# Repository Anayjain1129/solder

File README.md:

# Simple PCB that glows up
Submission for Solder YSWS

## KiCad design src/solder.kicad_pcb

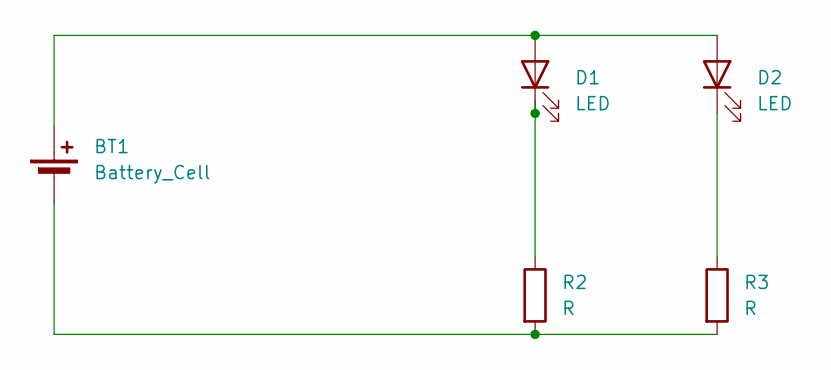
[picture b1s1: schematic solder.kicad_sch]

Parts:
BT1: Battery_Cell; BatteryHolder_Keystone_3034_1x20mm
D1, D2: LED; LED_D5.0mm
R2, R3: R; R_Axial_DIN0207_L6.3mm_D2.5mm_P7.62mm_Horizontal

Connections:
unnamed: BT1.1 (+), D1.2 (A), D2.2 (A)
unnamed: BT1.2 (-), R2.2, R3.2
unnamed: D1.1 (K), R2.1
unnamed: D2.1 (K), R3.1

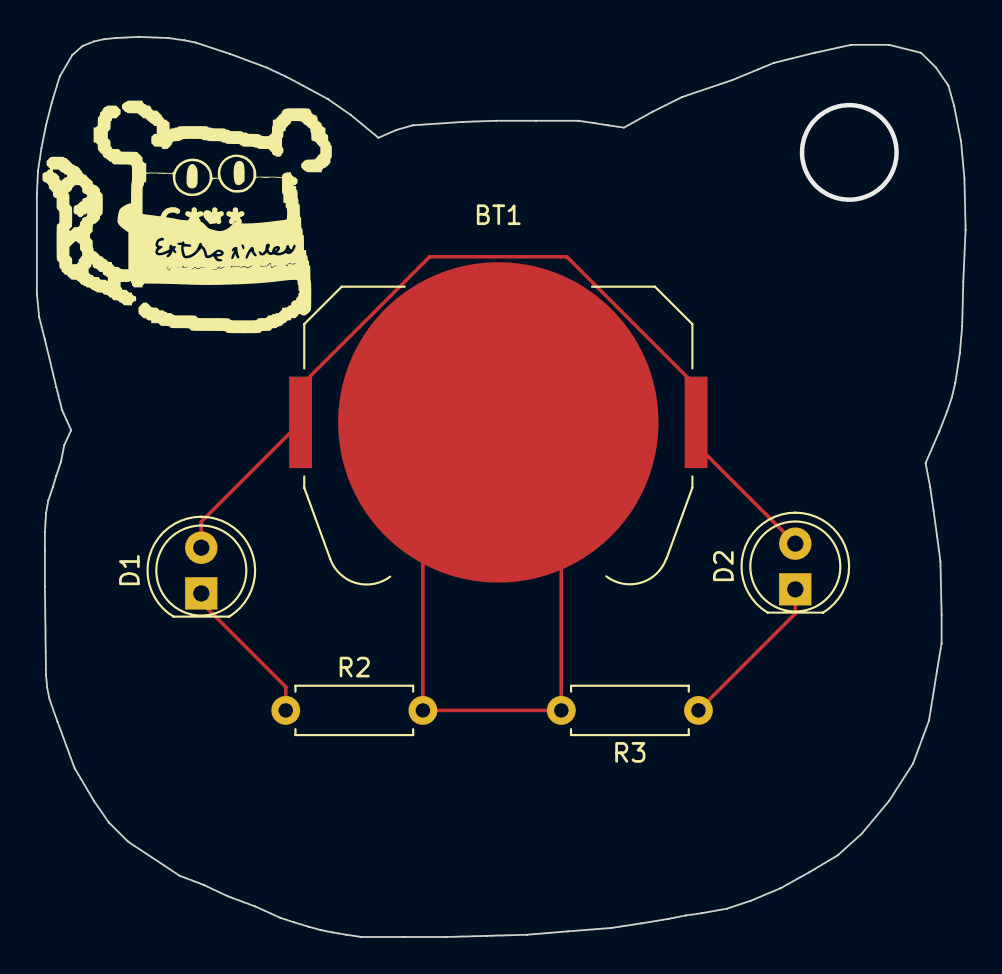
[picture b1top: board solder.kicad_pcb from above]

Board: 2 copper layers, 51.6 x 50.0 mm, 5 parts (0 on the bottom side), 4 nets.

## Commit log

2025-05-14 Update README.md
    readme
2025-05-14 Freakin images
2025-05-14 Add files via upload
    files
